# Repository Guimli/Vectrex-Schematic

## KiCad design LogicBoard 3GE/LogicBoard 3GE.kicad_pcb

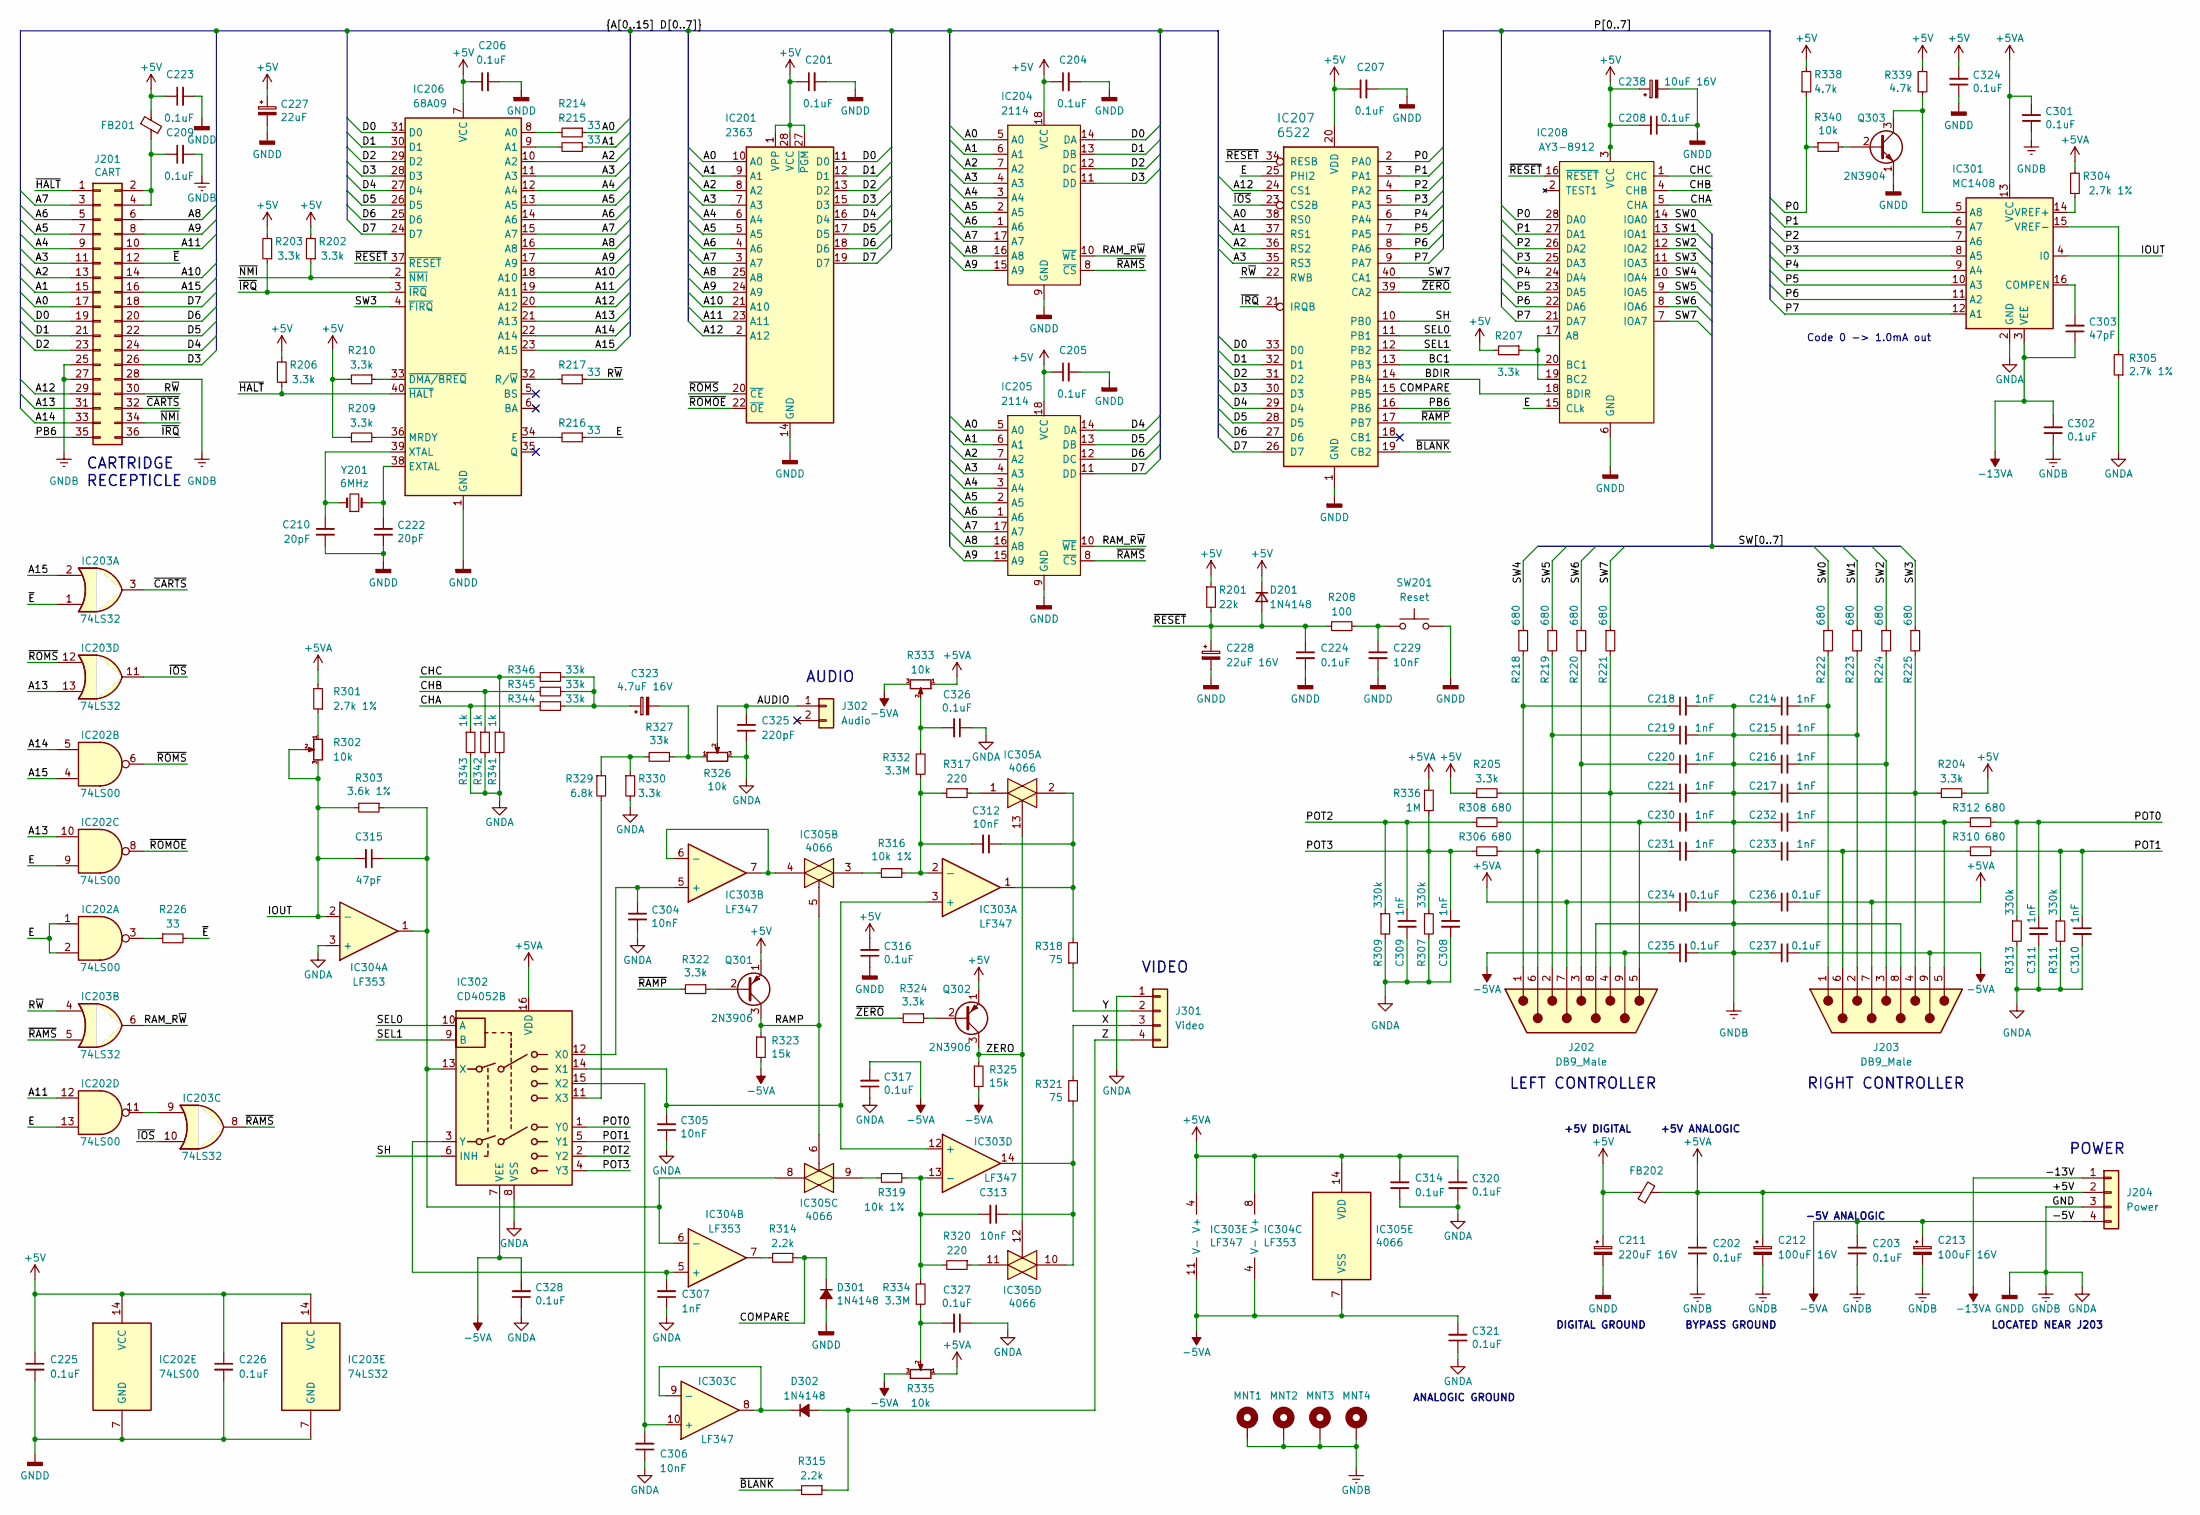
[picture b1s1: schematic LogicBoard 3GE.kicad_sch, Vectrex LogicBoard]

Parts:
C201, C204, C205, C206, C207, C208, C209, C223, C301, C302, C314, C316, C317, C320, C321, C324, C326, C327, C328: 0.1uF; C_Disc_D5.0mm_W2.5mm_P5.00mm; Mouser 581-SR215C104k
C202, C203, C224, C225, C226, C234, C235, C236, C237: 0.1uF; C_Disc_D5.0mm_W2.5mm_P5.00mm
C210, C222: 20pF; C_Disc_D5.0mm_W2.5mm_P5.00mm; Mouser 581-SR215A220kARTR1
C211: 220uF 16V; CP_Radial_D8.0mm_P2.50mm
C212, C213: 100uF 16V; CP_Radial_D8.0mm_P2.50mm
C214, C215, C216, C217, C218, C219, C220, C221, C230, C231, C232, C233: 1nF; C_Disc_D5.0mm_W2.5mm_P5.00mm
C227: 22uF; CP_Radial_Tantal_D5.5mm_P2.50mm; Mouser 647-UPW1A220MDD6TP
C228: 22uF 16V; CP_Radial_Tantal_D5.0mm_P2.50mm
C229: 10nF; C_Disc_D5.0mm_W2.5mm_P5.00mm
C238: 10uF 16V; CP_Radial_Tantal_D5.0mm_P2.50mm
C303, C315: 47pF; C_Disc_D5.0mm_W2.5mm_P5.00mm; Mouser 581-SR211A470JAR
C304, C305, C306: 10nF; C_Disc_D7.5mm_W5.0mm_P5.00mm; Mouser 810-FG28C0G2A472JRT6
C307, C308, C309, C310, C311: 1nF; C_Disc_D5.0mm_W2.5mm_P5.00mm; Mouser 581-SR211A102JAR
C312, C313: 10nF; C_Disc_D7.5mm_W5.0mm_P5.00mm; Mouser 810-FG28C0G2A103JRT6
C323: 4.7uF 16V; CP_Radial_D4.0mm_P2.00mm; Mouser 647-UkT1E4R7MDD1TD
C325: 220pF; C_Disc_D5.0mm_W2.5mm_P5.00mm; Mouser 581-SR211A221JAATR
D201: 1N4148; D_DO-34_SOD68_P12.70mm_Horizontal
D301, D302: 1N4148; D_DO-34_SOD68_P12.70mm_Horizontal; Mouser 512-1N4148
FB201, FB202: 96Ω @ 25MHz; L_Axial_L7.0mm_D3.3mm_P12.70mm_Horizontal_Fastron_MICC; Mouser 623-2743007112
IC201: 2363; DIP-28_W15.24mm
IC202: 74LS00; DIP-14_W7.62mm; Mouser 595-SN74LS00N
IC203: 74LS32; DIP-14_W7.62mm; Mouser 595-SN74LS32N
IC204, IC205: 2114; DIP-18_W7.62mm
IC206: 68A09; DIP-40_W15.24mm
IC207: 6522; DIP-40_W15.24mm; Mouser 955-W65C22S6TPG-14
IC208: AY3-8912; DIP-28_W15.24mm
IC301: MC1408; DIP-16_W7.62mm; Mouser 926-DAC0808LCN/NOPB
IC302: CD4052B; DIP-16_W7.62mm; Mouser 595-CD4052BE
IC303: LF347; DIP-14_W7.62mm; Mouser 595-LF347N
IC304: LF353; DIP-8_W7.62mm; Mouser 595-LF353P
IC305: 4066; DIP-14_W7.62mm; Mouser 595-CD4066BE
J201: CART; SULLINS_EBC18DRAS; Mouser 587-395-036
J202, J203: DB9_Male; DSUB-9_Male_Horizontal_Vectrex
J204: Power; Molex_KK-396_A-41791-0004_1x04_P3.96mm_Vertical
J301: Video; Molex_KK-254_AE-6410-04A_1x04_P2.54mm_Vertical
J302: Audio; Molex_KK-254_AE-6410-02A_1x02_P2.54mm_Vertical
MNT1, MNT2, MNT3, MNT4: MountingHole_Pad; MountingHole_3.5mm_Pad
Q301: 2N3906; TO-92L_Wide; Mouser 512-2N3906TA
Q302: 2N3906; TO-92_Wide; Mouser 512-2N3906TA
Q303: 2N3904; TO-92_Wide; Mouser 512-2N3904TA
R201: 22k; R_Axial_DIN0207_L6.3mm_D2.5mm_P12.70mm_Horizontal
R202, R203, R206, R207, R209, R210, R322, R324: 3.3k; R_Axial_DIN0207_L6.3mm_D2.5mm_P12.70mm_Horizontal; Mouser 603-CFR-25JR-523k3
R204, R205: 3.3k; R_Axial_DIN0207_L6.3mm_D2.5mm_P12.70mm_Horizontal
R208: 100; R_Axial_DIN0207_L6.3mm_D2.5mm_P12.70mm_Horizontal
R214, R215, R216, R217, R226: 33; R_Axial_DIN0207_L6.3mm_D2.5mm_P12.70mm_Horizontal; Mouser 603-CFR-25JR-5233R
R218, R219, R220, R221, R222, R223, R224, R225, R306, R308, R310, R312: 680; R_Axial_DIN0207_L6.3mm_D2.5mm_P12.70mm_Horizontal
R301, R304, R305: 2.7k 1%; R_Axial_DIN0207_L6.3mm_D2.5mm_P12.70mm_Horizontal; Mouser 603-MFR-25FRF522k49
R302: 10k; Potentiometer_ACP_CA14-H5_Horizontal; Mouser 531-PT10H-5k-S
R303: 3.6k 1%; R_Axial_DIN0207_L6.3mm_D2.5mm_P12.70mm_Horizontal; Mouser 603-MFR-25FRF52-2k61
R307, R309, R311, R313: 330k; R_Axial_DIN0207_L6.3mm_D2.5mm_P12.70mm_Horizontal; Mouser 603-CFR-25JR-52-330k
R314, R315: 2.2k; R_Axial_DIN0207_L6.3mm_D2.5mm_P12.70mm_Horizontal; Mouser 603-CFR-25JR-522k2
R316, R319: 10k 1%; R_Axial_DIN0207_L6.3mm_D2.5mm_P12.70mm_Horizontal; Mouser 603-MFR-25FRF5210k
R317, R320: 220; R_Axial_DIN0207_L6.3mm_D2.5mm_P12.70mm_Horizontal; Mouser 603-CFR-25JR-52220R
R318, R321: 75; R_Axial_DIN0207_L6.3mm_D2.5mm_P12.70mm_Horizontal; Mouser 603-MFR-25FTE52-3M3
R323, R325: 15k; R_Axial_DIN0207_L6.3mm_D2.5mm_P12.70mm_Horizontal; Mouser 603-CFR-25JR-5215k
R326: 10k; Potentiometer_UndLab_Horizontal; Mouser 531-PT10H-10k-S
R327, R344, R345, R346: 33k; R_Axial_DIN0207_L6.3mm_D2.5mm_P12.70mm_Horizontal; Mouser 603-CFR-25JR-52-33k
R329: 6.8k; R_Axial_DIN0207_L6.3mm_D2.5mm_P12.70mm_Horizontal; Mouser 603-CFR-25JR-52-33k
R330: 3.3k; R_Axial_DIN0207_L6.3mm_D2.5mm_P12.70mm_Horizontal; Mouser 603-CFR-25JR-52-33k
R332, R334: 3.3M; R_Axial_DIN0207_L6.3mm_D2.5mm_P12.70mm_Horizontal; Mouser 603-MFR-25FTE52-3M3
R333, R335: 10k; Potentiometer_ACP_CA14-H5_Horizontal; Mouser 531-PT10H-10k-S
R336: 1M; R_Axial_DIN0207_L6.3mm_D2.5mm_P12.70mm_Horizontal; Mouser 603-CFR-25JR-52-330k
R338, R339: 4.7k; R_Axial_DIN0207_L6.3mm_D2.5mm_P12.70mm_Horizontal; Mouser 603-CFR-25JR-524k7
R340: 10k; R_Axial_DIN0207_L6.3mm_D2.5mm_P12.70mm_Horizontal; Mouser 603-CFR-25JR-5210k
R341, R342, R343: 1k; R_Axial_DIN0207_L6.3mm_D2.5mm_P12.70mm_Horizontal; Mouser 603-CFR-25JR-521k
SW201: Reset; TestPoint_Bridge_Pitch5.08mm_Drill1.3mm
Y201: 6MHz; Crystal_HC49-U_Horizontal_1EP_style3; Mouser 815-AB-6-B2

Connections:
+5V: C201.1, C202.1, C204.1, C205.1, C206.1, C207.1, C208.2, C211.1, C212.1, C223.1, C225.1, C226.1, C227.1, C234.1, C236.2, C238.1, C301.2, C314.2, C316.2, C320.2, C324.2, D201.1 (k), FB201.1, FB202.1, FB202.2, IC201.1 (VPP), IC201.27 (~PGM), IC201.28 (VCC), IC202.14 (VCC), IC203.14 (VCC), IC204.18 (VCC), IC205.18 (VCC), IC206.7 (VCC), IC207.20 (VDD), IC208.3 (VCC), IC301.13 (VCC), IC302.16 (VDD), IC303.4 (V+), IC304.8 (V+), IC305.14 (VDD), J202.7, J203.7, J204.2, Q301.1 (E), Q302.1 (E), R201.1, R202.2, R203.2, R204.2, R205.1, R206.2, R207.2, R209.1, R210.2, R301.2, R304.2, R333.1, R335.1, R336.1, R338.2, R339.2
-5VA: C203.1, C213.1, C235.1, C237.2, C317.2, C321.2, C328.2, IC302.7 (VEE), IC303.11 (V-), IC304.4 (V-), IC305.7 (VSS), J202.9, J203.9, J204.4, R323.2, R325.2, R333.3, R335.3
-12VA: C302.2, C303.1, IC301.3 (VEE), J204.1
/A0: IC201.10 (A0), IC204.5 (A0), IC205.5 (A0), IC207.38 (RS0), J201.17, R214.1
/A1: IC201.9 (A1), IC204.6 (A1), IC205.6 (A1), IC207.37 (RS1), J201.15, R215.1
/A2: IC201.8 (A2), IC204.7 (A2), IC205.7 (A2), IC206.10 (A2), IC207.36 (RS2), J201.13
/A3: IC201.7 (A3), IC204.4 (A3), IC205.4 (A3), IC206.11 (A3), IC207.35 (RS3), J201.11
/A4: IC201.6 (A4), IC204.3 (A4), IC205.3 (A4), IC206.12 (A4), J201.9
/A5: IC201.5 (A5), IC204.2 (A5), IC205.2 (A5), IC206.13 (A5), J201.7
/A6: IC201.4 (A6), IC204.1 (A6), IC205.1 (A6), IC206.14 (A6), J201.5
/A7: IC201.3 (A7), IC204.17 (A7), IC205.17 (A7), IC206.15 (A7), J201.3
/A8: IC201.25 (A8), IC204.16 (A8), IC205.16 (A8), IC206.16 (A8), J201.6
/A9: IC201.24 (A9), IC204.15 (A9), IC205.15 (A9), IC206.17 (A9), J201.8
/A10: IC201.21 (A10), IC206.18 (A10), J201.14
/A11: IC201.23 (A11), IC202.12, IC206.19 (A11), J201.10
/A12: IC201.2 (A12), IC206.20 (A12), IC207.24 (CS1), J201.29
/A13: IC202.10, IC203.13, IC206.21 (A13), J201.31
/A14: IC202.5, IC206.22 (A14), J201.33
/A15: IC202.4, IC203.2, IC206.23 (A15), J201.16
/AUDIO: C325.2, J302.1, R326.2
/BC1: IC207.13 (PB3), IC208.20 (BC1)
/BDIR: IC207.14 (PB4), IC208.18 (BDIR)
/CHA: IC208.5 (CHA), R343.1, R344.2
/CHB: IC208.4 (CHB), R342.1, R345.2
/CHC: IC208.1 (CHC), R341.1, R346.2
/COMPARE: D301.1 (k), IC207.15 (PB5), R314.1
/D0: IC201.11 (D0), IC204.14 (DA), IC206.31 (D0), IC207.33 (D0), J201.19
/D1: IC201.12 (D1), IC204.13 (DB), IC206.30 (D1), IC207.32 (D1), J201.21
/D2: IC201.13 (D2), IC204.12 (DC), IC206.29 (D2), IC207.31 (D2), J201.23
/D3: IC201.15 (D3), IC204.11 (DD), IC206.28 (D3), IC207.30 (D3), J201.26
/D4: IC201.16 (D4), IC205.14 (DA), IC206.27 (D4), IC207.29 (D4), J201.24
/D5: IC201.17 (D5), IC205.13 (DB), IC206.26 (D5), IC207.28 (D5), J201.22
/D6: IC201.18 (D6), IC205.12 (DC), IC206.25 (D6), IC207.27 (D6), J201.20
/D7: IC201.19 (D7), IC205.11 (DD), IC206.24 (D7), IC207.26 (D7), J201.18
/E: IC202.1, IC202.2, IC202.9, IC202.13, IC207.25 (PHI2), IC208.15 (CLk), R216.1
/IOUT: C315.2, IC301.4 (I0), IC304.2 (-), R302.2, R302.3, R303.2
/P0: IC207.2 (PA0), IC208.28 (DA0), R338.1, R340.1
/P1: IC207.3 (PA1), IC208.27 (DA1), IC301.6 (A7)
/P2: IC207.4 (PA2), IC208.26 (DA2), IC301.7 (A6)
/P3: IC207.5 (PA3), IC208.25 (DA3), IC301.8 (A5)
/P4: IC207.6 (PA4), IC208.24 (DA4), IC301.9 (A4)
/P5: IC207.7 (PA5), IC208.23 (DA5), IC301.10 (A3)
/P6: IC207.8 (PA6), IC208.22 (DA6), IC301.11 (A2)
/P7: IC207.9 (PA7), IC208.21 (DA7), IC301.12 (A1)
/PB6: IC207.16 (PB6), J201.35
/POT0: C311.1, IC302.1 (Y0), R312.2, R313.1
/POT1: C310.1, IC302.5 (Y1), R310.2, R311.1
/POT2: C309.1, IC302.2 (Y2), R308.1, R309.1
/POT3: C308.1, IC302.4 (Y3), R306.1, R307.1, R336.2
/RAMP: IC305.5, IC305.6, Q301.3 (C), R323.1
/RAM_R~W: IC203.6, IC204.10 (~WE), IC205.10 (~WE)
/R~W: IC203.4, IC207.22 (RWB), J201.30, R217.1
/SEL0: IC207.11 (PB1), IC302.10 (A)
/SEL1: IC207.12 (PB2), IC302.9 (B)
/SH: IC207.10 (PB0), IC302.6 (INH)
/SW0: IC208.14 (IOA0), R222.1
/SW1: IC208.13 (IOA1), R223.1
/SW2: IC208.12 (IOA2), R224.1
/SW3: IC206.4 (~FIRQ), IC208.11 (IOA3), R225.1
/SW4: IC208.10 (IOA4), R218.1
/SW5: IC208.9 (IOA5), R219.1
/SW6: IC208.8 (IOA6), R220.1
/SW7: IC207.40 (CA1), IC208.7 (IOA7), R221.1
/X: J301.3, R321.2
/Y: J301.2, R318.1
/Z: D302.2 (A), J301.4, R315.1
/ZERO: IC305.12, IC305.13, Q302.3 (C), R325.1
/~BLANK: IC207.19 (CB2), R315.2
/~CARTS: IC203.3, J201.32
/~E: IC203.1, J201.12, R226.2
/~HALT: IC206.40 (~HALT), J201.1, R206.1
/~IOS: IC203.10, IC203.11, IC207.23 (CS2B)
/~IRQ: IC206.3 (~IRQ), IC207.21 (IRQB), J201.36, R203.1
/~NMI: IC206.2 (~NMI), J201.34, R202.1
/~RAMP: IC207.17 (PB7), R322.2
/~RAMS: IC203.5, IC203.8, IC204.8 (~CS), IC205.8 (~CS)
/~RESET: C224.1, C228.1, D201.2 (A), IC206.37 (~RESET), IC207.34 (RESB), IC208.16 (~RESET), R201.2, R208.1
/~ROMOE: IC201.22 (~OE), IC202.8
/~ROMS: IC201.20 (~CE), IC202.6, IC203.12
/~ZERO: IC207.39 (CA2), R324.2
GNDA: C201.2, C202.2, C203.2, C204.2, C205.2, C206.2, C207.2, C208.1, C209.2, C210.2, C211.2, C212.2, C213.2, C214.1, C215.1, C216.1, C217.1, C218.2, C219.2, C220.2, C221.2, C222.2, C223.2, C224.2, C225.2, C226.2, C227.2, C228.2, C229.2, C230.2, C231.2, C232.1, C233.1, C234.2, C235.2, C236.1, C237.1, C238.2, C301.1, C302.1, C304.2, C305.1, C306.1, C307.1, C308.2, C309.2, C310.2, C311.2, C314.1, C316.1, C317.1, C320.1, C321.1, C324.1, C325.1, C326.1, C327.1, C328.1, D301.2 (A), IC201.14 (GND), IC202.7 (GND), IC203.7 (GND), IC204.9 (GND), IC205.9 (GND), IC206.1 (GND), IC207.1 (GND), IC208.6 (GND), IC301.2 (GND), IC302.8 (VSS), IC304.3 (+), J201.25, J201.27, J201.28, J202.8, J203.8, J204.3, J301.1, MNT1.1, MNT2.1, MNT3.1, MNT4.1, Q303.1 (E), R305.1, R307.2, R309.2, R311.2, R313.2, R326.3, R330.2, R341.2, R342.2, R343.2, SW201.2
unnamed: C209.1, FB201.2, J201.2, J201.4
unnamed: C210.1, IC206.39 (XTAL), Y201.1
unnamed: C214.2, J203.1, R222.2
unnamed: C215.2, J203.2, R223.2
unnamed: C216.2, J203.3, R224.2
unnamed: C217.2, J203.4, R204.1, R225.2
unnamed: C218.1, J202.1, R218.2
unnamed: C219.1, J202.2, R219.2
unnamed: C220.1, J202.3, R220.2
unnamed: C221.1, J202.4, R205.2, R221.2
unnamed: C222.1, IC206.38 (EXTAL), Y201.2
unnamed: C229.1, R208.2, SW201.1
unnamed: C230.1, J202.5, R308.2
unnamed: C231.1, J202.6, R306.2
unnamed: C232.2, J203.5, R312.1
unnamed: C233.2, J203.6, R310.1
unnamed: C303.2, IC301.16 (COMPEN)
unnamed: C304.1, IC302.12 (X0), IC303.5 (+)
unnamed: C305.2, IC302.14 (X1), IC303.3 (+), IC303.12 (+)
unnamed: C306.2, IC302.15 (X2), IC303.10 (+)
unnamed: C307.2, IC302.3 (Y), IC304.5 (+)
unnamed: C312.1, IC303.1, IC305.2, R318.2
unnamed: C312.2, IC303.2 (-), R316.1, R317.2, R332.1
unnamed: C313.1, IC303.14, IC305.10, R321.1
unnamed: C313.2, IC303.13 (-), R319.1, R320.2, R334.2
unnamed: C315.1, IC302.13 (X), IC304.1, IC304.6 (-), IC305.8, R303.1
unnamed: C323.1, R344.1, R345.1, R346.1
unnamed: C323.2, R326.1, R327.1
unnamed: C326.2, R332.2, R333.2
unnamed: C327.2, R334.1, R335.2
unnamed: D302.1 (k), IC303.8, IC303.9 (-)
unnamed: IC202.3, R226.1
unnamed: IC202.11, IC203.9
unnamed: IC206.8 (A0), R214.2
unnamed: IC206.9 (A1), R215.2
unnamed: IC206.32 (R/~W), R217.2
unnamed: IC206.33 (~DMA/BREQ), R210.1
unnamed: IC206.34 (E), R216.2
unnamed: IC206.36 (MRDY), R209.2
unnamed: IC208.17 (A8), IC208.19 (BC2), R207.1
unnamed: IC301.5 (A8), Q303.3 (C), R339.1
unnamed: IC301.14 (VREF+), R304.1
unnamed: IC301.15 (VREF-), R305.2
unnamed: IC302.11 (X3), R329.2
unnamed: IC303.6 (-), IC303.7, IC305.4
unnamed: IC304.7, R314.2
unnamed: IC305.1, R317.1
unnamed: IC305.3, R316.2
unnamed: IC305.9, R319.2
unnamed: IC305.11, R320.1
unnamed: Q301.2 (B), R322.1
unnamed: Q302.2 (B), R324.1
unnamed: Q303.2 (B), R340.2
unnamed: R301.1, R302.1
unnamed: R327.2, R329.1, R330.1

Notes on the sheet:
LOCATED NEAR J203
DIGITAL GROUND
+5V DIGITAL
AUDIO
BYPASS GROUND
CARTRIDGE RECEPTICLE
-5V ANALOGIC
VIDEO
POWER
+5V ANALOGIC
ANALOGIC GROUND
RIGHT CONTROLLER
Code 0 -> 1.0mA out
LEFT CONTROLLER

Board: 2 copper layers, 162 parts (1 on the bottom side), 136 nets, no tracks yet.

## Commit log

2022-04-05 FIRQ & CA1
    Replace Label SW3 & SW7 by FIRQ & CA1 for more visibility.
2022-04-20 Minor location adjustment
    Minor location adjustment for better readability
2022-04-30 Minor cleannig
    Delete a redundant wire on IC208 pin 3
2022-07-18 Correct inversion on IC301 bus
2022-07-23 Add invisble label for BoardView
2022-07-29 Correct BoardView
2022-09-06 Added a comment about the 9V voltage which is not 9V...
2022-09-06 Rename -13V to -13VREF
2025-01-22 correction to the LM379 on the PowerBoard
    - Convert to Kicad 8
    - Correction to the LM379 on the PowerBoard and C405,C406,R404,R411
    - Correct value of F101
2025-01-22 Deleting unnecessary directories

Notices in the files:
LogicBoard 3GE/LogicBoard 3GE.kicad_sch:
or send a letter to Creative Commons, PO Box 1866, Mountain View, CA 94042, USA.
To view a copy of this license, visit http://creativecommons.org/licenses/by-sa/4.0
This work is licensed under the Creative Commons
